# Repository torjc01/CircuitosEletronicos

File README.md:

# Circuitos Eletrônicos
Repositório de projetos de circuitos eletrônicos e de design blocks, nos CADS Eagle e Kicad6.
<div align="center">
    
</div>

# Projetos

## Arduminimum

Implementação mínima do Arduino, que possa ser reutilizada em projetos de necessitem realizar uma montagem permanente e/ou reduzir o tamanho do seu footprint final. 

## Dawg-B-Gone

Uma implementação do famoso circuito "espanta-cachorros". Este circuito na prática é um circuito gerador de ultrasons, além do espectro audível por humanos. Mas para certos animais, em certas faixas de frequências, é repulsivo. Morcegos, ratos; moscas, mosquitos, e pernilongos; gambás, esquilos, enfim, toda sorte de de animal indesejável tem potencialmente uma faixa de frequência que funcionará como repelente. 

PS: A "denominação" do circuito é puramente tradicional, não queremos espantar os nossos amigos cachorros, portanto ficaremos fora da faixa de frequência a que eles são sensíveis. :laughing:

## Power Supply 

Implementação de um bloco de alimentação que seja capaz de receber um range de voltagens na entrada, e em seguida regular e distribuir outras voltagens na saída, que são comumente utilizadas em projetos com microcoltroladoras, como Arduino. O bloco de alimentação é usado como um `design block` para ser reutilizado em outros projetos de micro-eletrônica que necessitem trabalhar com diferentes voltagens. 

## Timer-Off

Prova de conceito da utilização de um CI 555 como switch para desligar um circuito, para auxiliar um colega do `Atelier La Patente` em um de seus projetos.

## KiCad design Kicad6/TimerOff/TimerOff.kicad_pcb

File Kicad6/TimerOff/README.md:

# Timer off

Sub-circuito baseado no CI NE555 cujo objetivo é desligar um circuito principal, apos decorrido um tempo pré-determinado pela combinçao dos valores de uma dupla de capacitor e resistor. 

## Reasoning

O timer é ativado pelo envio de corrente ao pin 2 (trigger) do NE555, que começa a encher o capacitor com carga, até 2/3 da capacidade; durante este periodo, o pin 3 (output) é ativado com a voltagem de saida. 

O delay para a desativaçao do circuito é determinado pela combinaçao de valores do resistor e do capacitor conectaos aos pins 6 e 7. Para um capacitor de valor fixo, digamos 470uF, ao se variar os valores dos resistores, obtemos a variaçao do tempo de delay de desligamento do circuito. Eu experimentei com alguns valores, e os resultados estao na tabela abaixo: 

| Resistor | Capacitor | Tempo de delay | 
|----------|-----------|----------------|
|33kΩ|470uF|15 seg|
|68kΩ|470uF|30 seg|
|122kΩ|470uF|1 min|
|320kΩ|470uF|2:30 min|
|580kΩ|470uF|5 min|
|800kΩ|470uF|7:30 min|
|1060kΩ|470uF|10 min|

Para o calculo dos valores, utilize a formula seguinte: 

```
T = 1.1 * R * C
```

## Schema 

## Bill of Mateirals

- 555 Timer IC
- Momentary Push Button Switch
- LED / ou outro dispositivo de saida
- 470uF Capacitor
- Resistors: 68K, 10K, 220R
- Breadboard
- Alguns jumpers para Breadboard 
- (5-12)V Power Supply
- Potenciometro (Opcional)
- Modulo Relê (Opcional)

## Referências 

NE555 https://www.ti.com/lit/ds/symlink/ne555.pdf

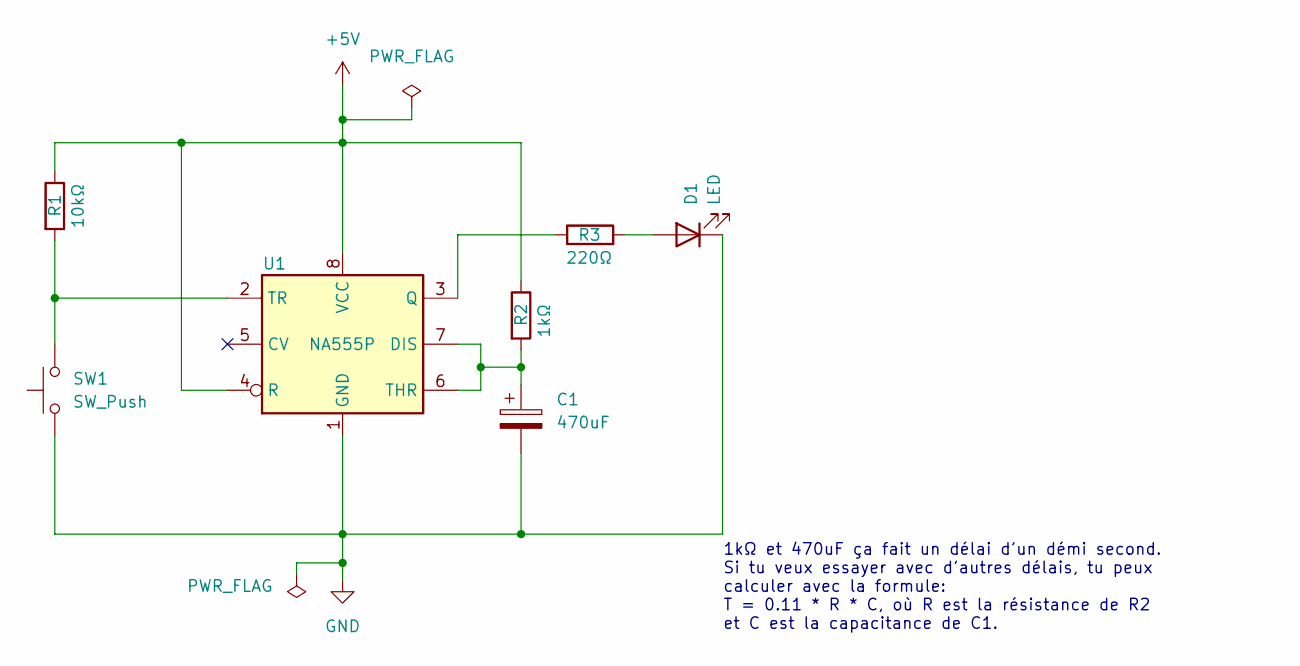
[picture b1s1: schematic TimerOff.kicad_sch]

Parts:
C1: 470uF; CP_Radial_D10.0mm_P2.50mm
D1: LED; LED_D3.0mm_Clear
R1: 10kΩ; R_Axial_DIN0207_L6.3mm_D2.5mm_P7.62mm_Horizontal
R2: 1kΩ; R_Axial_DIN0207_L6.3mm_D2.5mm_P7.62mm_Horizontal
R3: 220Ω; R_Axial_DIN0207_L6.3mm_D2.5mm_P7.62mm_Horizontal
SW1: SW_Push; SW_Tactile_Straight_KSL0Axx1LFTR
U1: NA555P; SOIC-8_3.9x4.9mm_P1.27mm

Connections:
+5V: R1.1, R2.1, U1.4 (R), U1.8 (VCC)
GND: C1.2, D1.1 (K), SW1.1, U1.1 (GND)
unnamed: C1.1, R2.2, U1.6 (THR), U1.7 (DIS)
unnamed: D1.2 (A), R3.2
unnamed: R1.2, SW1.2, U1.2 (TR)
unnamed: R3.1, U1.3 (Q)

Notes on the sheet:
1kΩ et 470uF ça fait un délai d'un démi second. Si tu veux essayer avec d'autres délais, tu peux calculer avec la formule: T = 0.11 * R * C, où R est la résistance de R2 et C est la capacitance de C1.

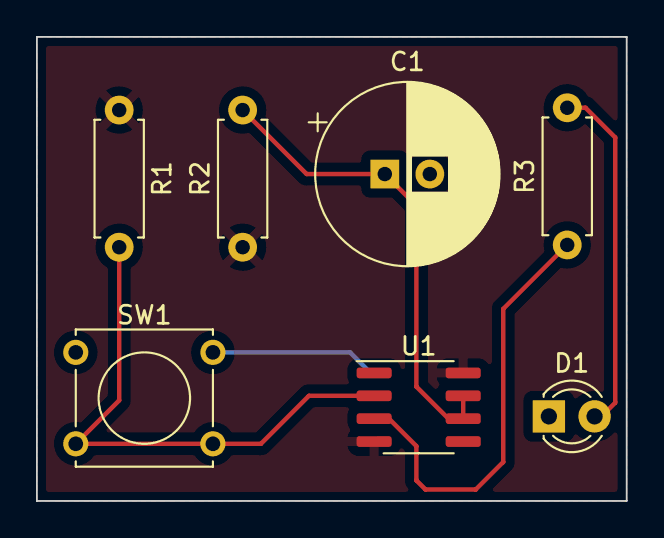
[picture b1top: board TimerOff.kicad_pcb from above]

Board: 2 copper layers, 32.8 x 25.8 mm, 7 parts (0 on the bottom side), 6 nets.

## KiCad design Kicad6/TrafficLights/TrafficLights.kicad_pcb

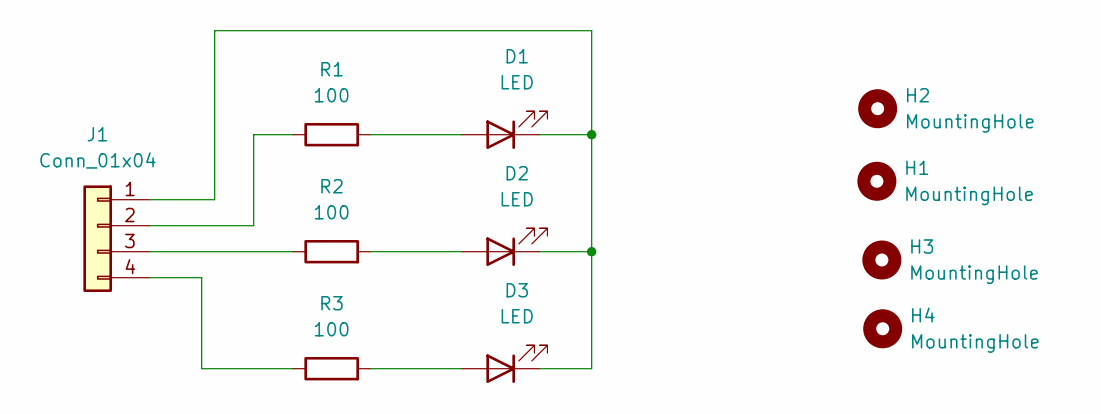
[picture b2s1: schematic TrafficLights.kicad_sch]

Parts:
D1, D2, D3: LED; LED_D3.0mm
H1, H2, H3, H4: MountingHole; MountingHole_2.5mm_Pad
J1: Conn_01x04; PinHeader_1x04_P2.54mm_Horizontal
R1, R2, R3: 100; R_Axial_DIN0204_L3.6mm_D1.6mm_P5.08mm_Horizontal

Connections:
unnamed: D1.1 (K), D2.1 (K), D3.1 (K), J1.1
unnamed: D1.2 (A), R1.2
unnamed: D2.2 (A), R2.2
unnamed: D3.2 (A), R3.2
unnamed: J1.2, R1.1
unnamed: J1.3, R2.1
unnamed: J1.4, R3.1

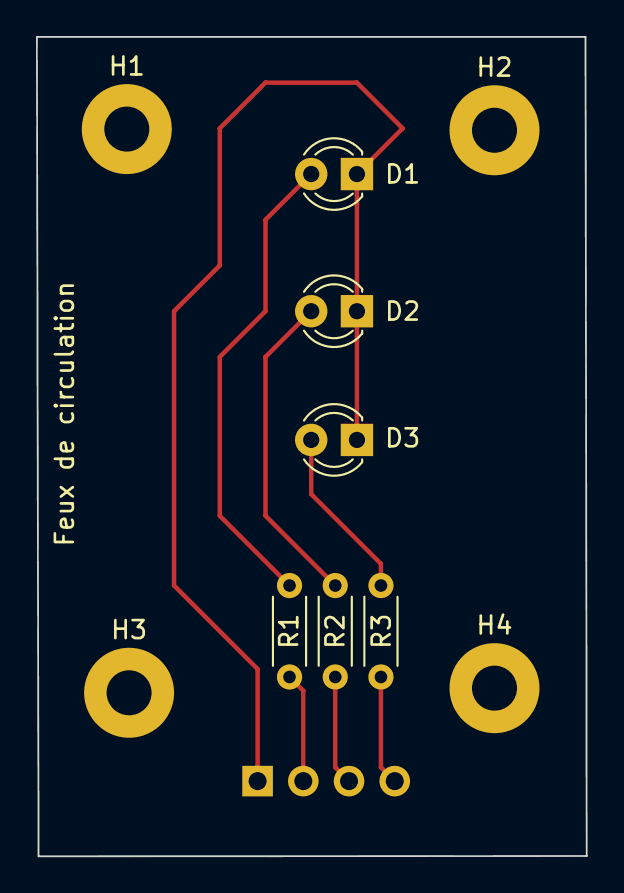
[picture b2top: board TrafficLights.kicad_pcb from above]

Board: 2 copper layers, 30.5 x 45.5 mm, 11 parts (1 on the bottom side), 7 nets.

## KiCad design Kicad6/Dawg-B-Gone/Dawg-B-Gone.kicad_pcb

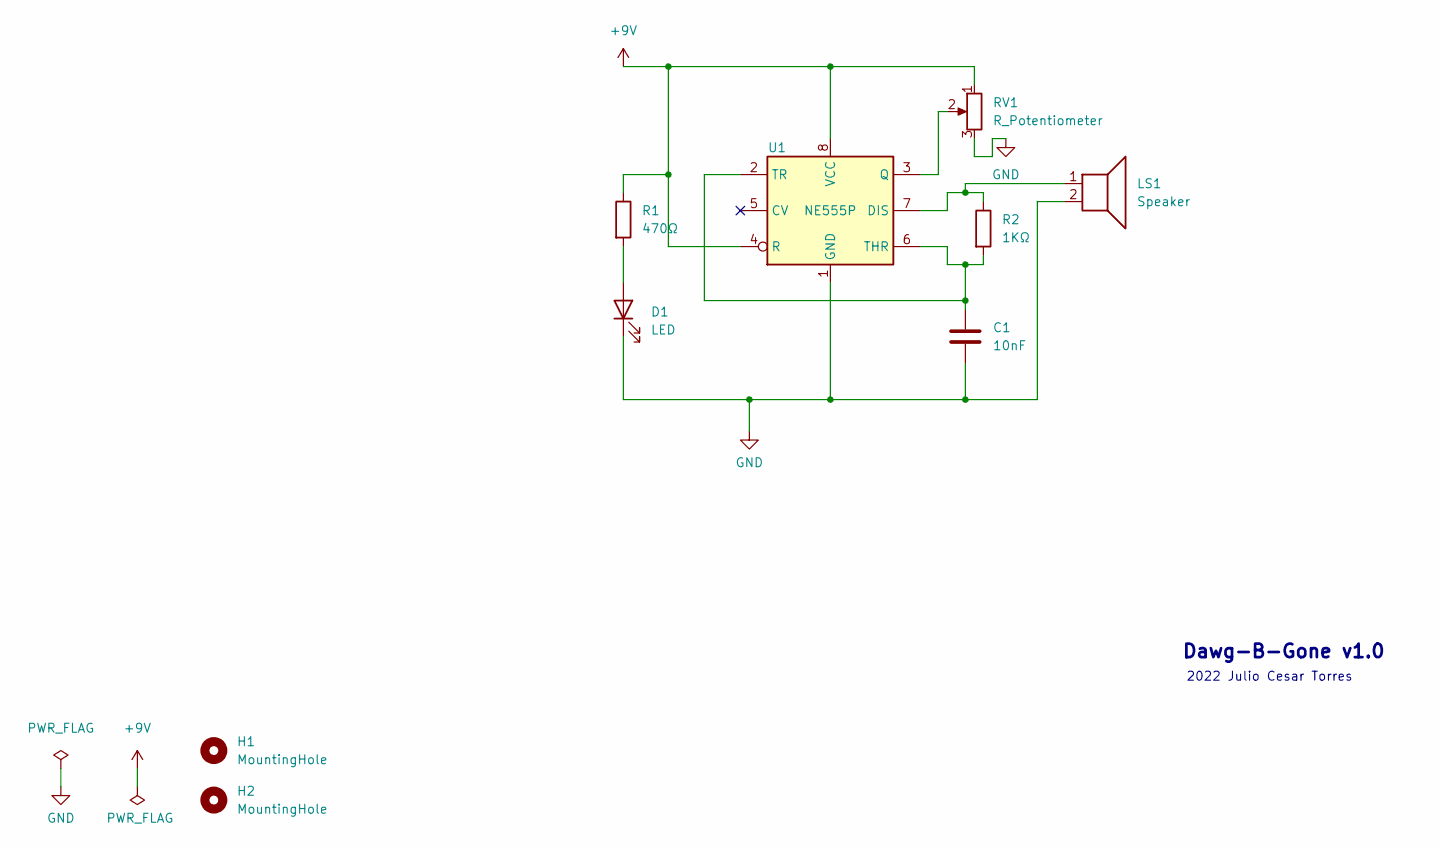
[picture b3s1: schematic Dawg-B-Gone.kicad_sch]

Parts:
C1: 10nF; C_Disc_D3.0mm_W1.6mm_P2.50mm
D1: LED; LED_D3.0mm
H1, H2: MountingHole; MountingHole_2.2mm_M2_Pad_Via
LS1: Speaker; Buzzer_TDK_PS1240P02BT_D12.2mm_H6.5mm
R1: 470Ω; R_Axial_DIN0207_L6.3mm_D2.5mm_P10.16mm_Horizontal
R2: 1KΩ; R_Axial_DIN0207_L6.3mm_D2.5mm_P10.16mm_Horizontal
RV1: R_Potentiometer; Potentiometer_Alps_RK163_Single_Horizontal
U1: NE555P; DIP-8_W7.62mm

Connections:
+9V: R1.1, RV1.1, U1.4 (R), U1.8 (VCC)
GND: C1.1, D1.1 (K), LS1.2, RV1.3, U1.1 (GND)
unnamed: C1.2, R2.2, U1.2 (TR), U1.6 (THR)
unnamed: D1.2 (A), R1.2
unnamed: LS1.1, R2.1, U1.7 (DIS)
unnamed: RV1.2, U1.3 (Q)

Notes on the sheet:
2022 Julio Cesar Torres
Dawg-B-Gone v1.0

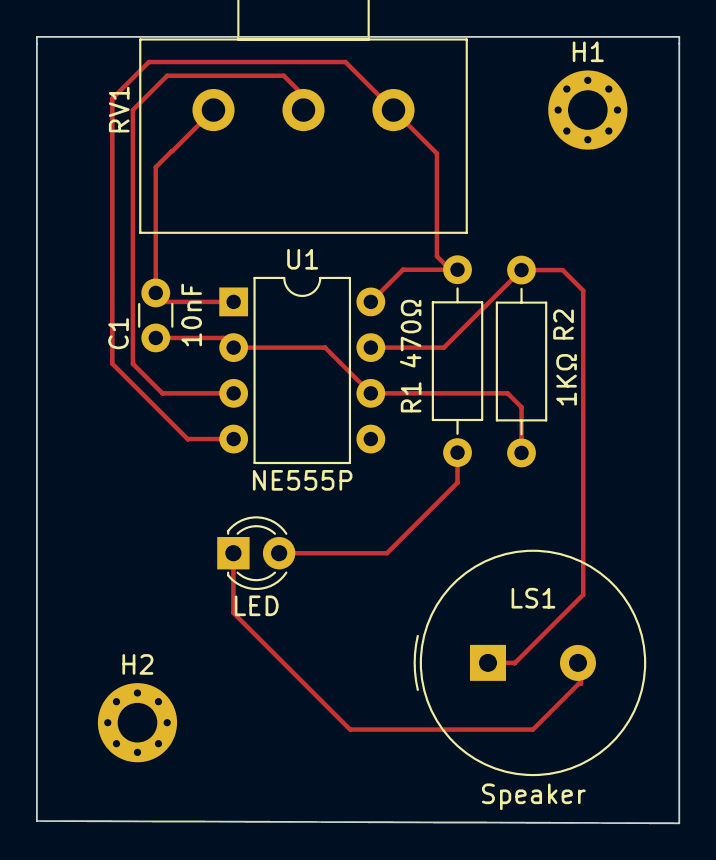
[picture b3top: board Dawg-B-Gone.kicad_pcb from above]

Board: 2 copper layers, 35.7 x 43.7 mm, 9 parts (0 on the bottom side), 6 nets.

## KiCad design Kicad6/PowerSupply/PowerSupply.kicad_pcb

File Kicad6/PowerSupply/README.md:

# Power Suppy for microcontrollers v.1.0

Fonte de alimentação para projetos de microcontroladores. A entrada de corrente se dá via adaptador de 9 a 12 V

**Caracteristicas**

Vin: 9V-12V  
Vout: +9V, +5V, +3.3V

Tensões disponíveis:
- +9V em AREF
- +5V diretamente de Vout 
- +3.3V regulado em Vout

Conector de entrada: barrel jack 2.5mm, polaridade positiva ao centro

Switch on/off 

Proteção contra sobrecarga e corrente reversa 

## Schematics 

## Board

### Projeto 
Frente 

Verso  

### Versão do fabricante 

Frente 

Verso 

### Visão 3D

Frente 

Verso

## Plano de soldagem 

* Etapas a serem seguidas
    - Resistores
        - Orientar a banda de tolerância para a direita ou para o alto, conforme a posição do resistor
    - Diodo 
        - Observar a polaridade 
    - Switch 
    - Jumpers 
    - Capacitores 
        - Observar as polaridades 
    - CI 7805
        - Observar orientação dos pinos 
    - Jack 
        - Quantidade de solda suficiente para os pinos 

## Referências

### Datasheets

LM7805 - Voltage regulator 5V
 
https://www.ti.com/general/docs/suppproductinfo.tsp?distId=10&gotoUrl=https%3A%2F%2Fwww.ti.com%2Flit%2Fgpn%2Flm340

LM1086 - Voltage regulator 3.3V 

https://www.ti.com/lit/ds/symlink/lm1086.pdf?HQS=dis-mous-null-mousermode-dsf-pf-null-wwe&ts=1667479620648&ref_url=https%253A%252F%252Fwww.mouser.fr%252F

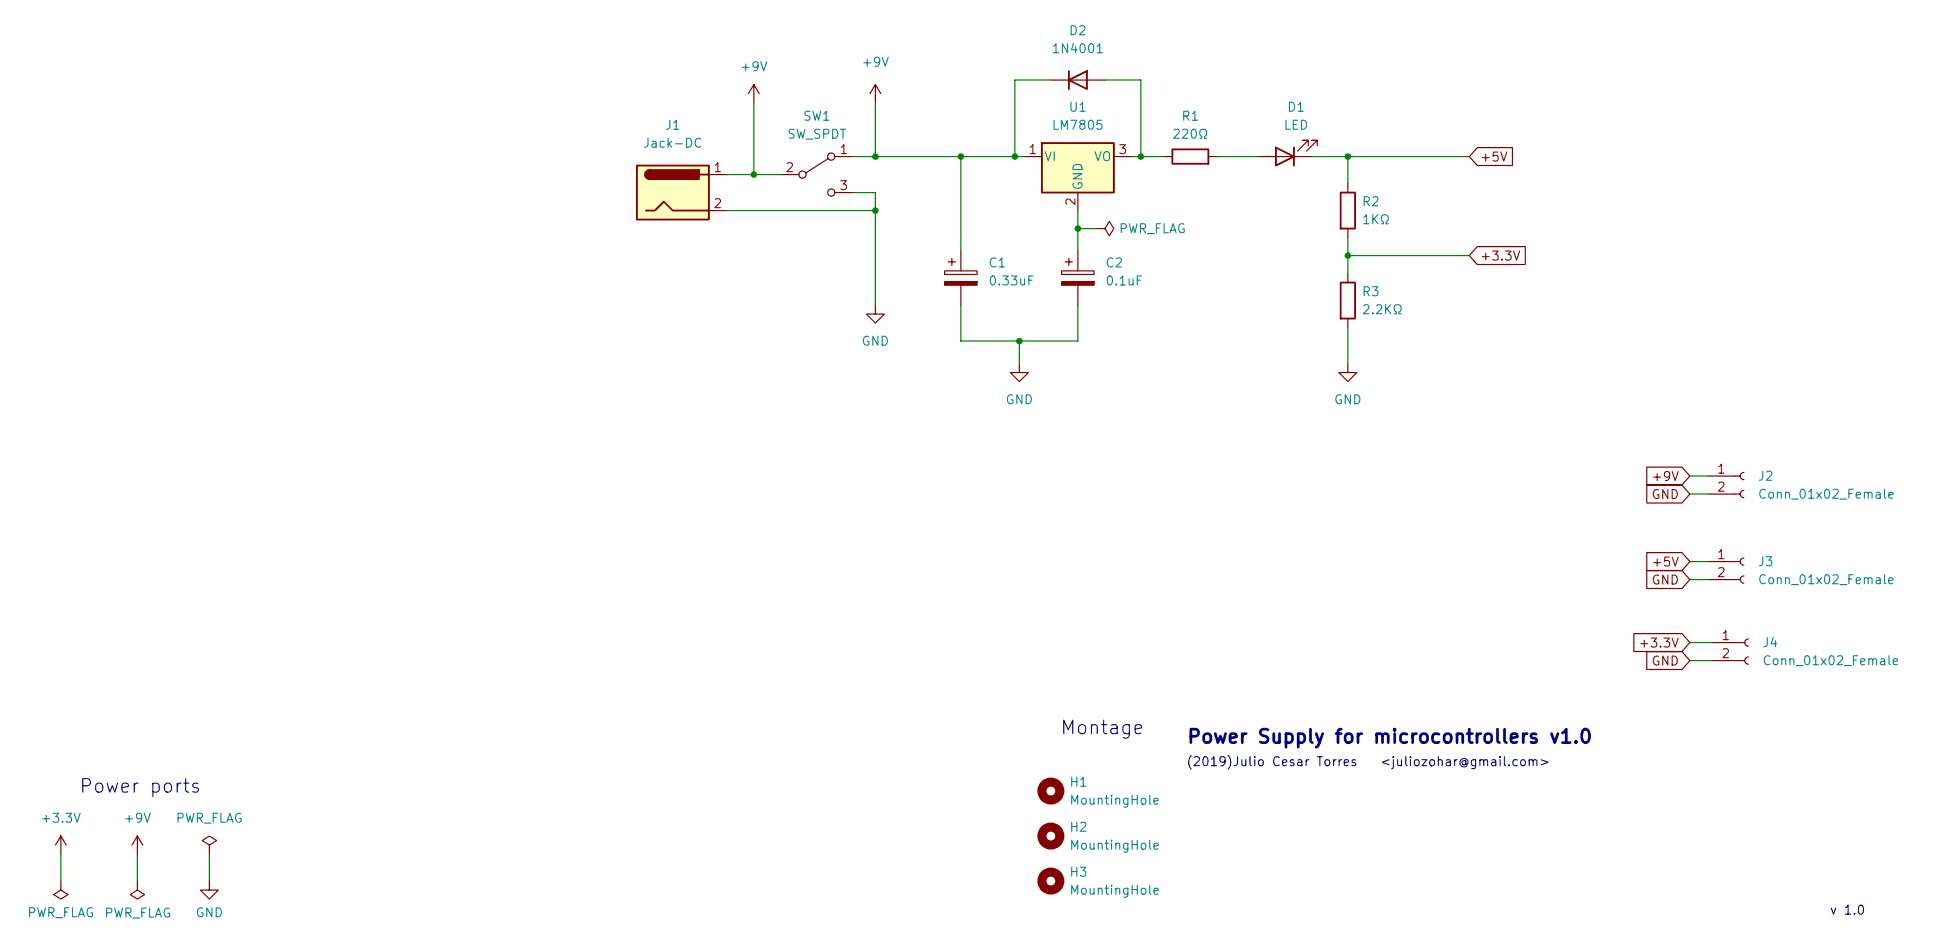
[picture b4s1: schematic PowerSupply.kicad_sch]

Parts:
C1: 0.33uF; CP_Radial_D5.0mm_P2.00mm
C2: 0.1uF; CP_Radial_D5.0mm_P2.00mm
D1: LED; LED_D3.0mm
D2: 1N4001; D_DO-41_SOD81_P10.16mm_Horizontal
H1, H2, H3: MountingHole; MountingHole_2.2mm_M2_Pad_Via
J1: Jack-DC; BarrelJack_Horizontal
J2, J3, J4: Conn_01x02_Female; PinHeader_1x02_P2.54mm_Vertical
R1: 220Ω; R_Axial_DIN0207_L6.3mm_D2.5mm_P10.16mm_Horizontal
R2: 1KΩ; R_Axial_DIN0207_L6.3mm_D2.5mm_P10.16mm_Horizontal
R3: 2.2KΩ; R_Axial_DIN0207_L6.3mm_D2.5mm_P10.16mm_Horizontal
SW1: SW_SPDT; PinHeader_1x03_P2.54mm_Vertical
U1: LM7805; TO-220-3_Vertical

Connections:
+3.3V: J4.1, R2.2, R3.1
+5V: D1.1 (K), J3.1, R2.1
+9V: C1.1, D2.1 (K), J1.1, J2.1, SW1.1 (A), SW1.2 (B), U1.1 (VI)
GND: C1.2, C2.2, J1.2, J2.2, J3.2, J4.2, R3.2, SW1.3 (C)
unnamed: C2.1, U1.2 (GND)
unnamed: D1.2 (A), R1.2
unnamed: D2.2 (A), R1.1, U1.3 (VO)

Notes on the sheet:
<juliozohar@gmail.com>
Power ports
Montage
v 1.0
Power Supply for microcontrollers v1.0
(2019)Julio Cesar Torres

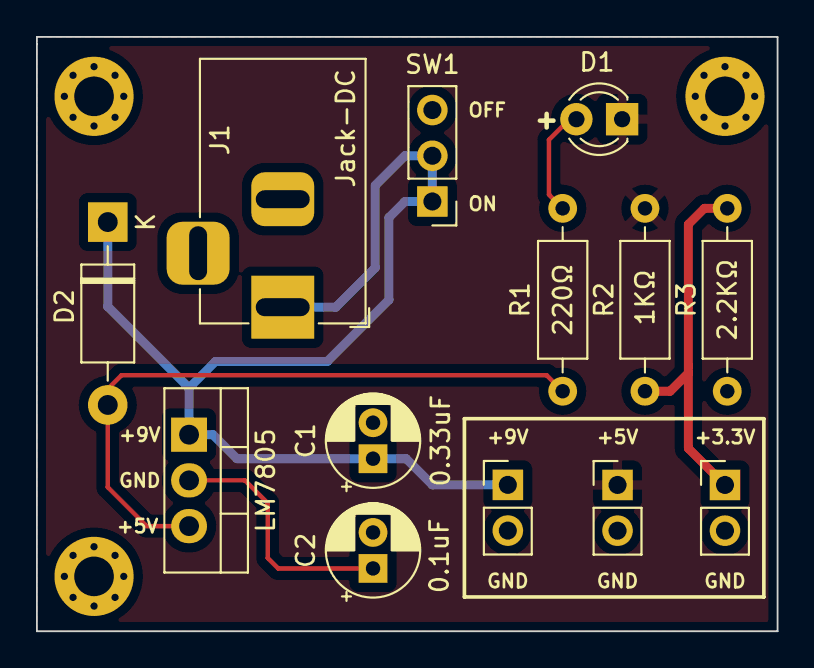
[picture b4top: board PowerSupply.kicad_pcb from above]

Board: 2 copper layers, 41.1 x 33.0 mm, 16 parts (0 on the bottom side), 7 nets.

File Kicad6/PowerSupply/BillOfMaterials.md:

# BOM - Bill of materials

| Qtd  | Componente | Valor | Referencia web | Notas |
|------|------------|-------|----------------|-------|
|01 | Barrel Jack 2.5mm |2.5mm |https://www.digikey.ca/en/products/detail/sparkfun-electroni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 | Polaridade positiva centro|
|01 | Slide Switch SPDT | |https://www.digikey.ca/en/products/detail/e-switch/EG1218/101726 ||
|01 | Cap eletrolítico |0.33uF|||
|01 | Cap eletrolítico |0.1uF|||
|01 | Resistor |220Ω|||
|01 | Resistor |1KΩ|||
|01 | Resistor |2.2KΩ|||
|01 | LED |3mm|||
|01 | Diodo retificador 1N4001|50V 1A||Filtro de proteção tensão de entrada|
|01 | CI LM7805 |||Regulador de tensão|

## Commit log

2022-10-14 [func] Criacao do repositorio
2022-10-14 [func] inclusao das imagens de referencia comuns
2022-10-14 [func] inclui novas exclusoes no gitignore-s
2022-10-14 [func] criacao da BOM da fonte
2022-10-14 [func] adiciona lista de materiais
2022-10-14 [doc] incrementa readme do projeto
2022-10-15 [doc] incrementa readme do projeto com imagens
2022-10-20 [func] inclui projeto de circuito Arduminimum
2022-10-20 [func] inclui microcontroladora no schematic
2022-10-20 [func] inclui projeto de PCB Dawg-B-Gone
2022-10-20 [func] inclui projeto de PCB TrafficLights
2022-10-25 [func] melhorias do circuito; inclusao de novas partes
2022-10-25 [func] adiciona arquivos auto gerados
2022-10-25 inclui arquivo de especificacoes
2022-10-25 [func] adiciona novos componentes ao circuito; documenta
2022-10-26 [doc] adiciona diagrama de correspondencia
2022-10-26 [func] evolui o documento de schema
2022-10-27 [func] inclui repositorio TimerOff
2022-10-27 [func] adiciona especificacoes ao projeto
2022-10-27 [doc] inclui o BOM do TimerOff
2022-10-27 [doc] inclui informacoes sobre resistores
2022-11-01 [doc] inclui tabela de unidades de grandeza
2022-11-01 [doc] complementa caracteristicas do power supply
2022-11-03 [doc] ajustes da documentação
2022-11-30 [doc] descrição das etapas a serem seguidas na soldagem dos componentes
2022-11-30 [doc] evolucao da documentacao
